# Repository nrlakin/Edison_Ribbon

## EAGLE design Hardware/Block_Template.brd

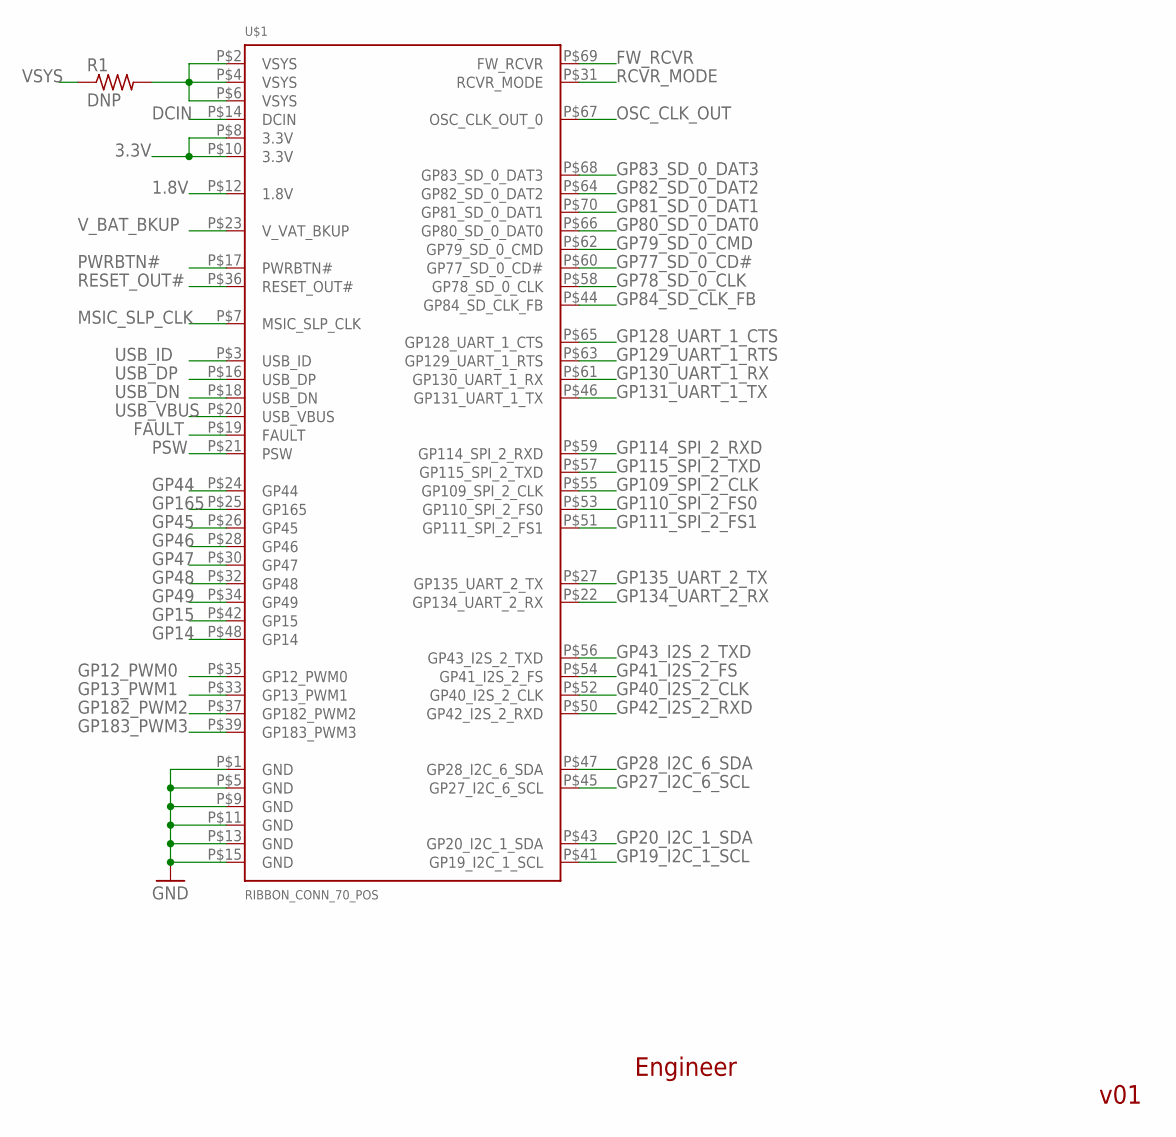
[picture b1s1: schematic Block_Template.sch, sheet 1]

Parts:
R1: DNP; R0402
U$1: RIBBON_CONN_70_POS

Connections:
1.8V: U$1.P$12 (1.8V); also elsewhere on the board
3.3V: U$1.P$8 (3.3V), U$1.P$10 (3.3V); also elsewhere on the board
DCIN: U$1.P$14 (DCIN); also elsewhere on the board
FAULT: U$1.P$19 (FAULT); also elsewhere on the board
FW_RCVR: U$1.P$69 (FW_RCVR); also elsewhere on the board
GND: U$1.P$1 (GND), U$1.P$5 (GND), U$1.P$9 (GND), U$1.P$11 (GND), U$1.P$13 (GND), U$1.P$15 (GND); also elsewhere on the board
GP12_PWM0: U$1.P$35 (GP12_PWM0); also elsewhere on the board
GP13_PWM1: U$1.P$33 (GP13_PWM1); also elsewhere on the board
GP14: U$1.P$48 (GP14); also elsewhere on the board
GP15: U$1.P$42 (GP15); also elsewhere on the board
GP19_I2C_1_SCL: U$1.P$41 (GP19_I2C_1_SCL); also elsewhere on the board
GP20_I2C_1_SDA: U$1.P$43 (GP20_I2C_1_SDA); also elsewhere on the board
GP27_I2C_6_SCL: U$1.P$45 (GP27_I2C_6_SCL); also elsewhere on the board
GP28_I2C_6_SDA: U$1.P$47 (GP28_I2C_6_SDA); also elsewhere on the board
GP40_I2S_2_CLK: U$1.P$52 (GP40_I2S_2_CLK); also elsewhere on the board
GP41_I2S_2_FS: U$1.P$54 (GP41_I2S_2_FS); also elsewhere on the board
GP42_I2S_2_RXD: U$1.P$50 (GP42_I2S_2_RXD); also elsewhere on the board
GP43_I2S_2_TXD: U$1.P$56 (GP43_I2S_2_TXD); also elsewhere on the board
GP44: U$1.P$24 (GP44); also elsewhere on the board
GP45: U$1.P$26 (GP45); also elsewhere on the board
GP46: U$1.P$28 (GP46); also elsewhere on the board
GP47: U$1.P$30 (GP47); also elsewhere on the board
GP48: U$1.P$32 (GP48); also elsewhere on the board
GP49: U$1.P$34 (GP49); also elsewhere on the board
GP77_SD_0_CD#: U$1.P$60 (GP77_SD_0_CD#); also elsewhere on the board
GP78_SD_0_CLK: U$1.P$58 (GP78_SD_0_CLK); also elsewhere on the board
GP79_SD_0_CMD: U$1.P$62 (GP79_SD_0_CMD); also elsewhere on the board
GP80_SD_0_DAT0: U$1.P$66 (GP80_SD_0_DAT0); also elsewhere on the board
GP81_SD_0_DAT1: U$1.P$70 (GP81_SD_0_DAT1); also elsewhere on the board
GP82_SD_0_DAT2: U$1.P$64 (GP82_SD_0_DAT2); also elsewhere on the board
GP83_SD_0_DAT3: U$1.P$68 (GP83_SD_0_DAT3); also elsewhere on the board
GP84_SD_CLK_FB: U$1.P$44 (GP84_SD_CLK_FB); also elsewhere on the board
GP109_SPI_2_CLK: U$1.P$55 (GP109_SPI_2_CLK); also elsewhere on the board
GP110_SPI_2_FS0: U$1.P$53 (GP110_SPI_2_FS0); also elsewhere on the board
GP111_SPI_2_FS1: U$1.P$51 (GP111_SPI_2_FS1); also elsewhere on the board
GP114_SPI_2_RXD: U$1.P$59 (GP114_SPI_2_RXD); also elsewhere on the board
GP115_SPI_2_TXD: U$1.P$57 (GP115_SPI_2_TXD); also elsewhere on the board
GP128_UART_1_CTS: U$1.P$65 (GP128_UART_1_CTS); also elsewhere on the board
GP129_UART_1_RTS: U$1.P$63 (GP129_UART_1_RTS); also elsewhere on the board
GP130_UART_1_RX: U$1.P$61 (GP130_UART_1_RX); also elsewhere on the board
GP131_UART_1_TX: U$1.P$46 (GP131_UART_1_TX); also elsewhere on the board
GP134_UART_2_RX: U$1.P$22 (GP134_UART_2_RX); also elsewhere on the board
GP135_UART_2_TX: U$1.P$27 (GP135_UART_2_TX); also elsewhere on the board
GP165: U$1.P$25 (GP165); also elsewhere on the board
GP182_PWM2: U$1.P$37 (GP182_PWM2); also elsewhere on the board
GP183_PWM3: U$1.P$39 (GP183_PWM3); also elsewhere on the board
MSIC_SLP_CLK: U$1.P$7 (MSIC_SLP_CLK); also elsewhere on the board
unnamed: R1.2, U$1.P$2 (VSYS), U$1.P$4 (VSYS), U$1.P$6 (VSYS)
OSC_CLK_OUT: U$1.P$67 (OSC_CLK_OUT_0); also elsewhere on the board
PSW: U$1.P$21 (PSW); also elsewhere on the board
PWRBTN#: U$1.P$17 (PWRBTN#); also elsewhere on the board
RCVR_MODE: U$1.P$31 (RCVR_MODE); also elsewhere on the board
RESET_OUT#: U$1.P$36 (RESET_OUT#); also elsewhere on the board
USB_DN: U$1.P$18 (USB_DN); also elsewhere on the board
USB_DP: U$1.P$16 (USB_DP); also elsewhere on the board
USB_ID: U$1.P$3 (USB_ID); also elsewhere on the board
USB_VBUS: U$1.P$20 (USB_VBUS); also elsewhere on the board
VSYS: R1.1; also elsewhere on the board
V_BAT_BKUP: U$1.P$23 (V_VAT_BKUP); also elsewhere on the board

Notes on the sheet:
v01
Engineer

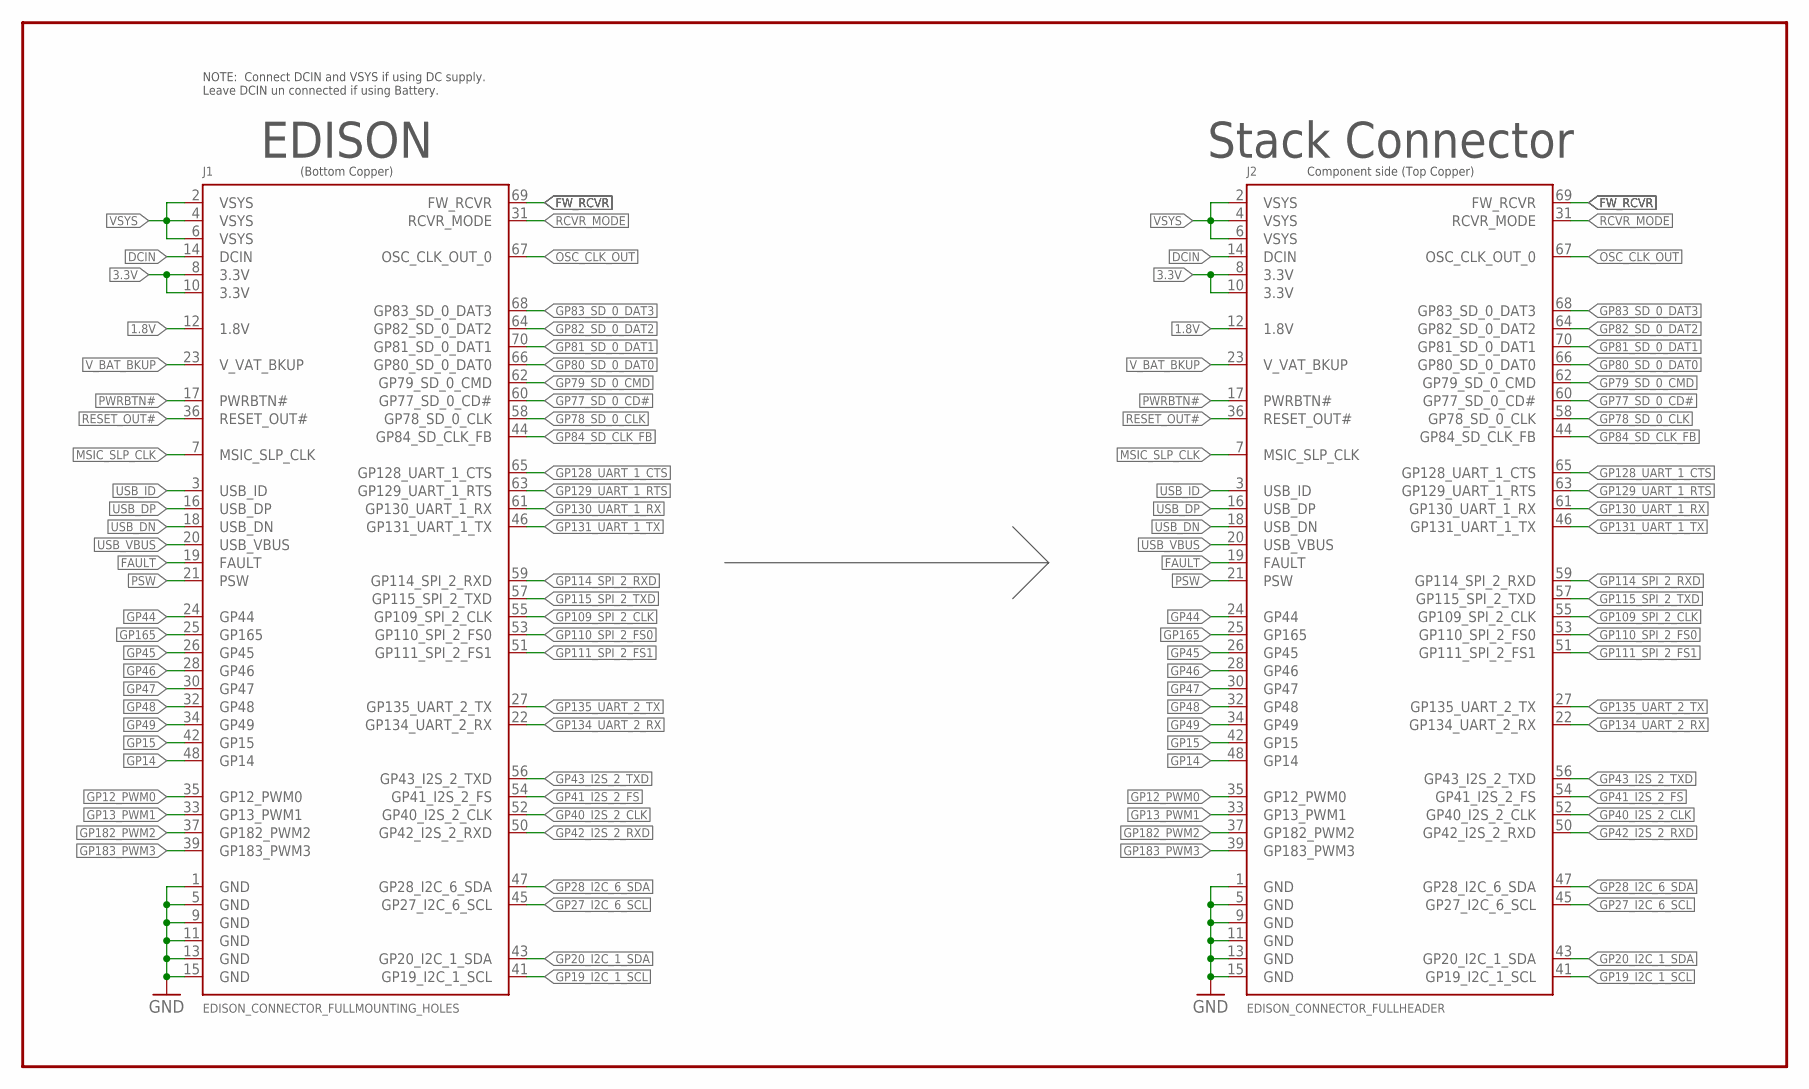
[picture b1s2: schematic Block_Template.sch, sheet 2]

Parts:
J1: EDISON_CONNECTOR_FULLMOUNTING_HOLES; EDISON_DAUGHTER
J2: EDISON_CONNECTOR_FULLHEADER; DF40C-70DP-0.4(51)

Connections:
1.8V: J1.12 (1.8V), J2.12 (1.8V); also elsewhere on the board
3.3V: J1.8 (3.3V), J1.10 (3.3V), J2.8 (3.3V), J2.10 (3.3V); also elsewhere on the board
DCIN: J1.14 (DCIN), J2.14 (DCIN); also elsewhere on the board
FAULT: J1.19 (FAULT), J2.19 (FAULT); also elsewhere on the board
FW_RCVR: J1.69 (FW_RCVR), J2.69 (FW_RCVR); also elsewhere on the board
GND: J1.1 (GND), J1.5 (GND), J1.9 (GND), J1.11 (GND), J1.13 (GND), J1.15 (GND), J2.1 (GND), J2.5 (GND), J2.9 (GND), J2.11 (GND), J2.13 (GND), J2.15 (GND); also elsewhere on the board
GP12_PWM0: J1.35 (GP12_PWM0), J2.35 (GP12_PWM0); also elsewhere on the board
GP13_PWM1: J1.33 (GP13_PWM1), J2.33 (GP13_PWM1); also elsewhere on the board
GP14: J1.48 (GP14), J2.48 (GP14); also elsewhere on the board
GP15: J1.42 (GP15), J2.42 (GP15); also elsewhere on the board
GP19_I2C_1_SCL: J1.41 (GP19_I2C_1_SCL), J2.41 (GP19_I2C_1_SCL); also elsewhere on the board
GP20_I2C_1_SDA: J1.43 (GP20_I2C_1_SDA), J2.43 (GP20_I2C_1_SDA); also elsewhere on the board
GP27_I2C_6_SCL: J1.45 (GP27_I2C_6_SCL), J2.45 (GP27_I2C_6_SCL); also elsewhere on the board
GP28_I2C_6_SDA: J1.47 (GP28_I2C_6_SDA), J2.47 (GP28_I2C_6_SDA); also elsewhere on the board
GP40_I2S_2_CLK: J1.52 (GP40_I2S_2_CLK), J2.52 (GP40_I2S_2_CLK); also elsewhere on the board
GP41_I2S_2_FS: J1.54 (GP41_I2S_2_FS), J2.54 (GP41_I2S_2_FS); also elsewhere on the board
GP42_I2S_2_RXD: J1.50 (GP42_I2S_2_RXD), J2.50 (GP42_I2S_2_RXD); also elsewhere on the board
GP43_I2S_2_TXD: J1.56 (GP43_I2S_2_TXD), J2.56 (GP43_I2S_2_TXD); also elsewhere on the board
GP44: J1.24 (GP44), J2.24 (GP44); also elsewhere on the board
GP45: J1.26 (GP45), J2.26 (GP45); also elsewhere on the board
GP46: J1.28 (GP46), J2.28 (GP46); also elsewhere on the board
GP47: J1.30 (GP47), J2.30 (GP47); also elsewhere on the board
GP48: J1.32 (GP48), J2.32 (GP48); also elsewhere on the board
GP49: J1.34 (GP49), J2.34 (GP49); also elsewhere on the board
GP77_SD_0_CD#: J1.60 (GP77_SD_0_CD#), J2.60 (GP77_SD_0_CD#); also elsewhere on the board
GP78_SD_0_CLK: J1.58 (GP78_SD_0_CLK), J2.58 (GP78_SD_0_CLK); also elsewhere on the board
GP79_SD_0_CMD: J1.62 (GP79_SD_0_CMD), J2.62 (GP79_SD_0_CMD); also elsewhere on the board
GP80_SD_0_DAT0: J1.66 (GP80_SD_0_DAT0), J2.66 (GP80_SD_0_DAT0); also elsewhere on the board
GP81_SD_0_DAT1: J1.70 (GP81_SD_0_DAT1), J2.70 (GP81_SD_0_DAT1); also elsewhere on the board
GP82_SD_0_DAT2: J1.64 (GP82_SD_0_DAT2), J2.64 (GP82_SD_0_DAT2); also elsewhere on the board
GP83_SD_0_DAT3: J1.68 (GP83_SD_0_DAT3), J2.68 (GP83_SD_0_DAT3); also elsewhere on the board
GP84_SD_CLK_FB: J1.44 (GP84_SD_CLK_FB), J2.44 (GP84_SD_CLK_FB); also elsewhere on the board
GP109_SPI_2_CLK: J1.55 (GP109_SPI_2_CLK), J2.55 (GP109_SPI_2_CLK); also elsewhere on the board
GP110_SPI_2_FS0: J1.53 (GP110_SPI_2_FS0), J2.53 (GP110_SPI_2_FS0); also elsewhere on the board
GP111_SPI_2_FS1: J1.51 (GP111_SPI_2_FS1), J2.51 (GP111_SPI_2_FS1); also elsewhere on the board
GP114_SPI_2_RXD: J1.59 (GP114_SPI_2_RXD), J2.59 (GP114_SPI_2_RXD); also elsewhere on the board
GP115_SPI_2_TXD: J1.57 (GP115_SPI_2_TXD), J2.57 (GP115_SPI_2_TXD); also elsewhere on the board
GP128_UART_1_CTS: J1.65 (GP128_UART_1_CTS), J2.65 (GP128_UART_1_CTS); also elsewhere on the board
GP129_UART_1_RTS: J1.63 (GP129_UART_1_RTS), J2.63 (GP129_UART_1_RTS); also elsewhere on the board
GP130_UART_1_RX: J1.61 (GP130_UART_1_RX), J2.61 (GP130_UART_1_RX); also elsewhere on the board
GP131_UART_1_TX: J1.46 (GP131_UART_1_TX), J2.46 (GP131_UART_1_TX); also elsewhere on the board
GP134_UART_2_RX: J1.22 (GP134_UART_2_RX), J2.22 (GP134_UART_2_RX); also elsewhere on the board
GP135_UART_2_TX: J1.27 (GP135_UART_2_TX), J2.27 (GP135_UART_2_TX); also elsewhere on the board
GP165: J1.25 (GP165), J2.25 (GP165); also elsewhere on the board
GP182_PWM2: J1.37 (GP182_PWM2), J2.37 (GP182_PWM2); also elsewhere on the board
GP183_PWM3: J1.39 (GP183_PWM3), J2.39 (GP183_PWM3); also elsewhere on the board
MSIC_SLP_CLK: J1.7 (MSIC_SLP_CLK), J2.7 (MSIC_SLP_CLK); also elsewhere on the board
OSC_CLK_OUT: J1.67 (OSC_CLK_OUT_0), J2.67 (OSC_CLK_OUT_0); also elsewhere on the board
PSW: J1.21 (PSW), J2.21 (PSW); also elsewhere on the board
PWRBTN#: J1.17 (PWRBTN#), J2.17 (PWRBTN#); also elsewhere on the board
RCVR_MODE: J1.31 (RCVR_MODE), J2.31 (RCVR_MODE); also elsewhere on the board
RESET_OUT#: J1.36 (RESET_OUT#), J2.36 (RESET_OUT#); also elsewhere on the board
USB_DN: J1.18 (USB_DN), J2.18 (USB_DN); also elsewhere on the board
USB_DP: J1.16 (USB_DP), J2.16 (USB_DP); also elsewhere on the board
USB_ID: J1.3 (USB_ID), J2.3 (USB_ID); also elsewhere on the board
USB_VBUS: J1.20 (USB_VBUS), J2.20 (USB_VBUS); also elsewhere on the board
VSYS: J1.2 (VSYS), J1.4 (VSYS), J1.6 (VSYS), J2.2 (VSYS), J2.4 (VSYS), J2.6 (VSYS); also elsewhere on the board
V_BAT_BKUP: J1.23 (V_VAT_BKUP), J2.23 (V_VAT_BKUP); also elsewhere on the board

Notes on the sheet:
EDISON
Stack Connector
Component side (Top Copper)
(Bottom Copper)
NOTE: Connect DCIN and VSYS if using DC supply. Leave DCIN un connected if using Battery.

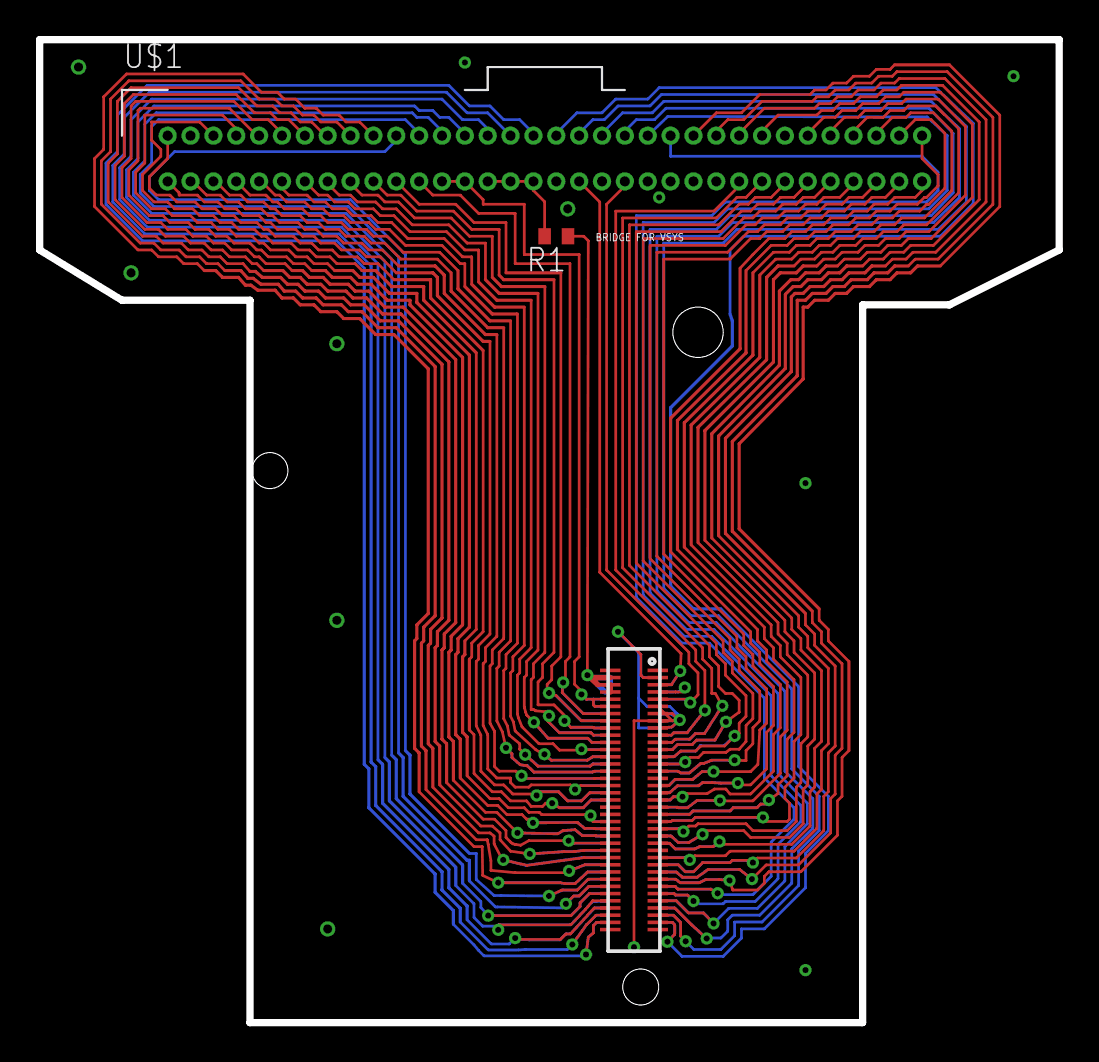
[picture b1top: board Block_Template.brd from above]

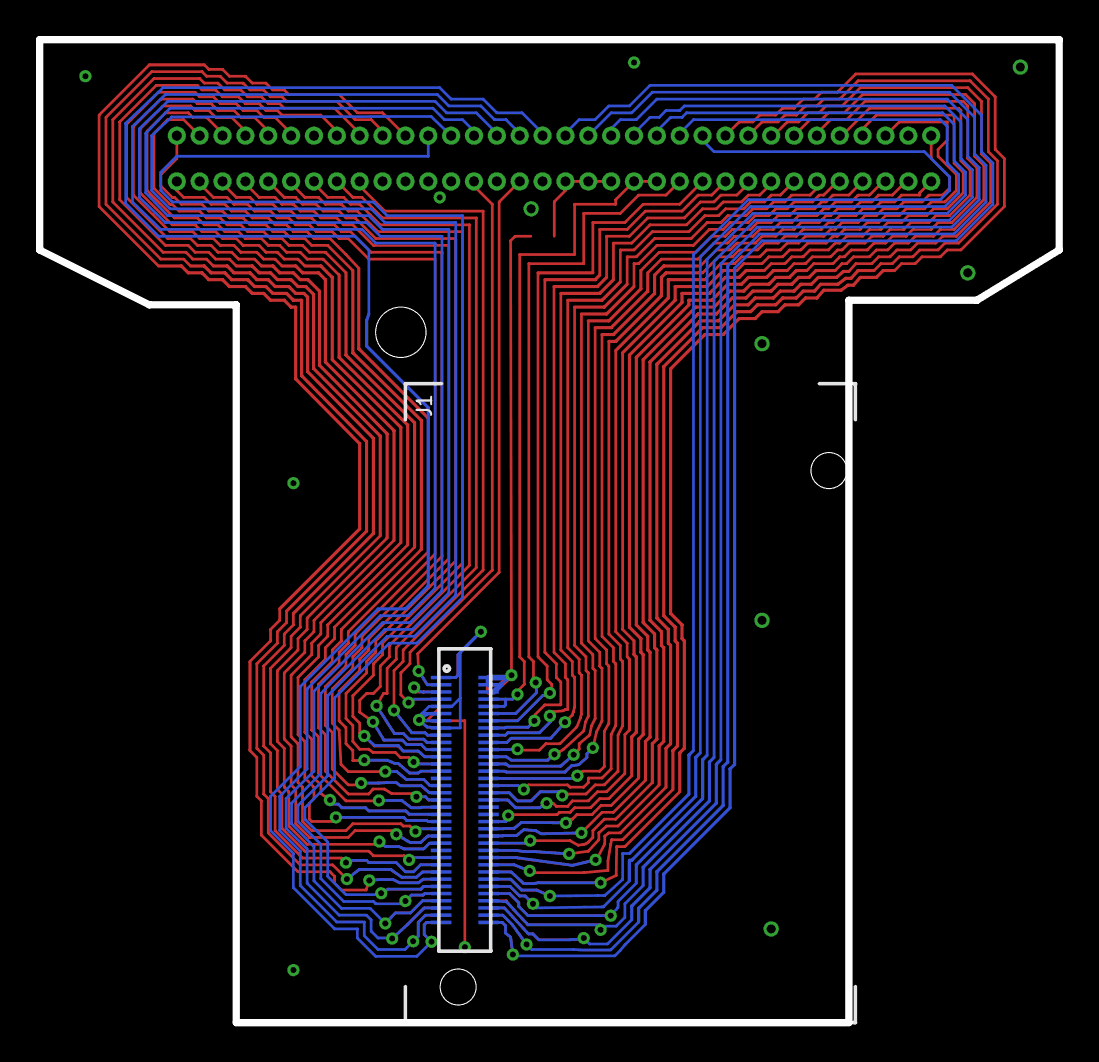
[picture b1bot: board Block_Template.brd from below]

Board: 2 copper layers, 56.6 x 54.6 mm, 4 parts (2 on the bottom side), 59 nets.

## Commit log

2016-04-24 initial cut
2016-04-24 nets defined, need final decision on connector
2016-04-25 ready for manufacture
2016-04-26 off to fab.
